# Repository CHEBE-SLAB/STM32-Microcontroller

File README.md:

# STM32-Microcontroller
STM32 Microcontroller project files using KiCAD, Gerber files included

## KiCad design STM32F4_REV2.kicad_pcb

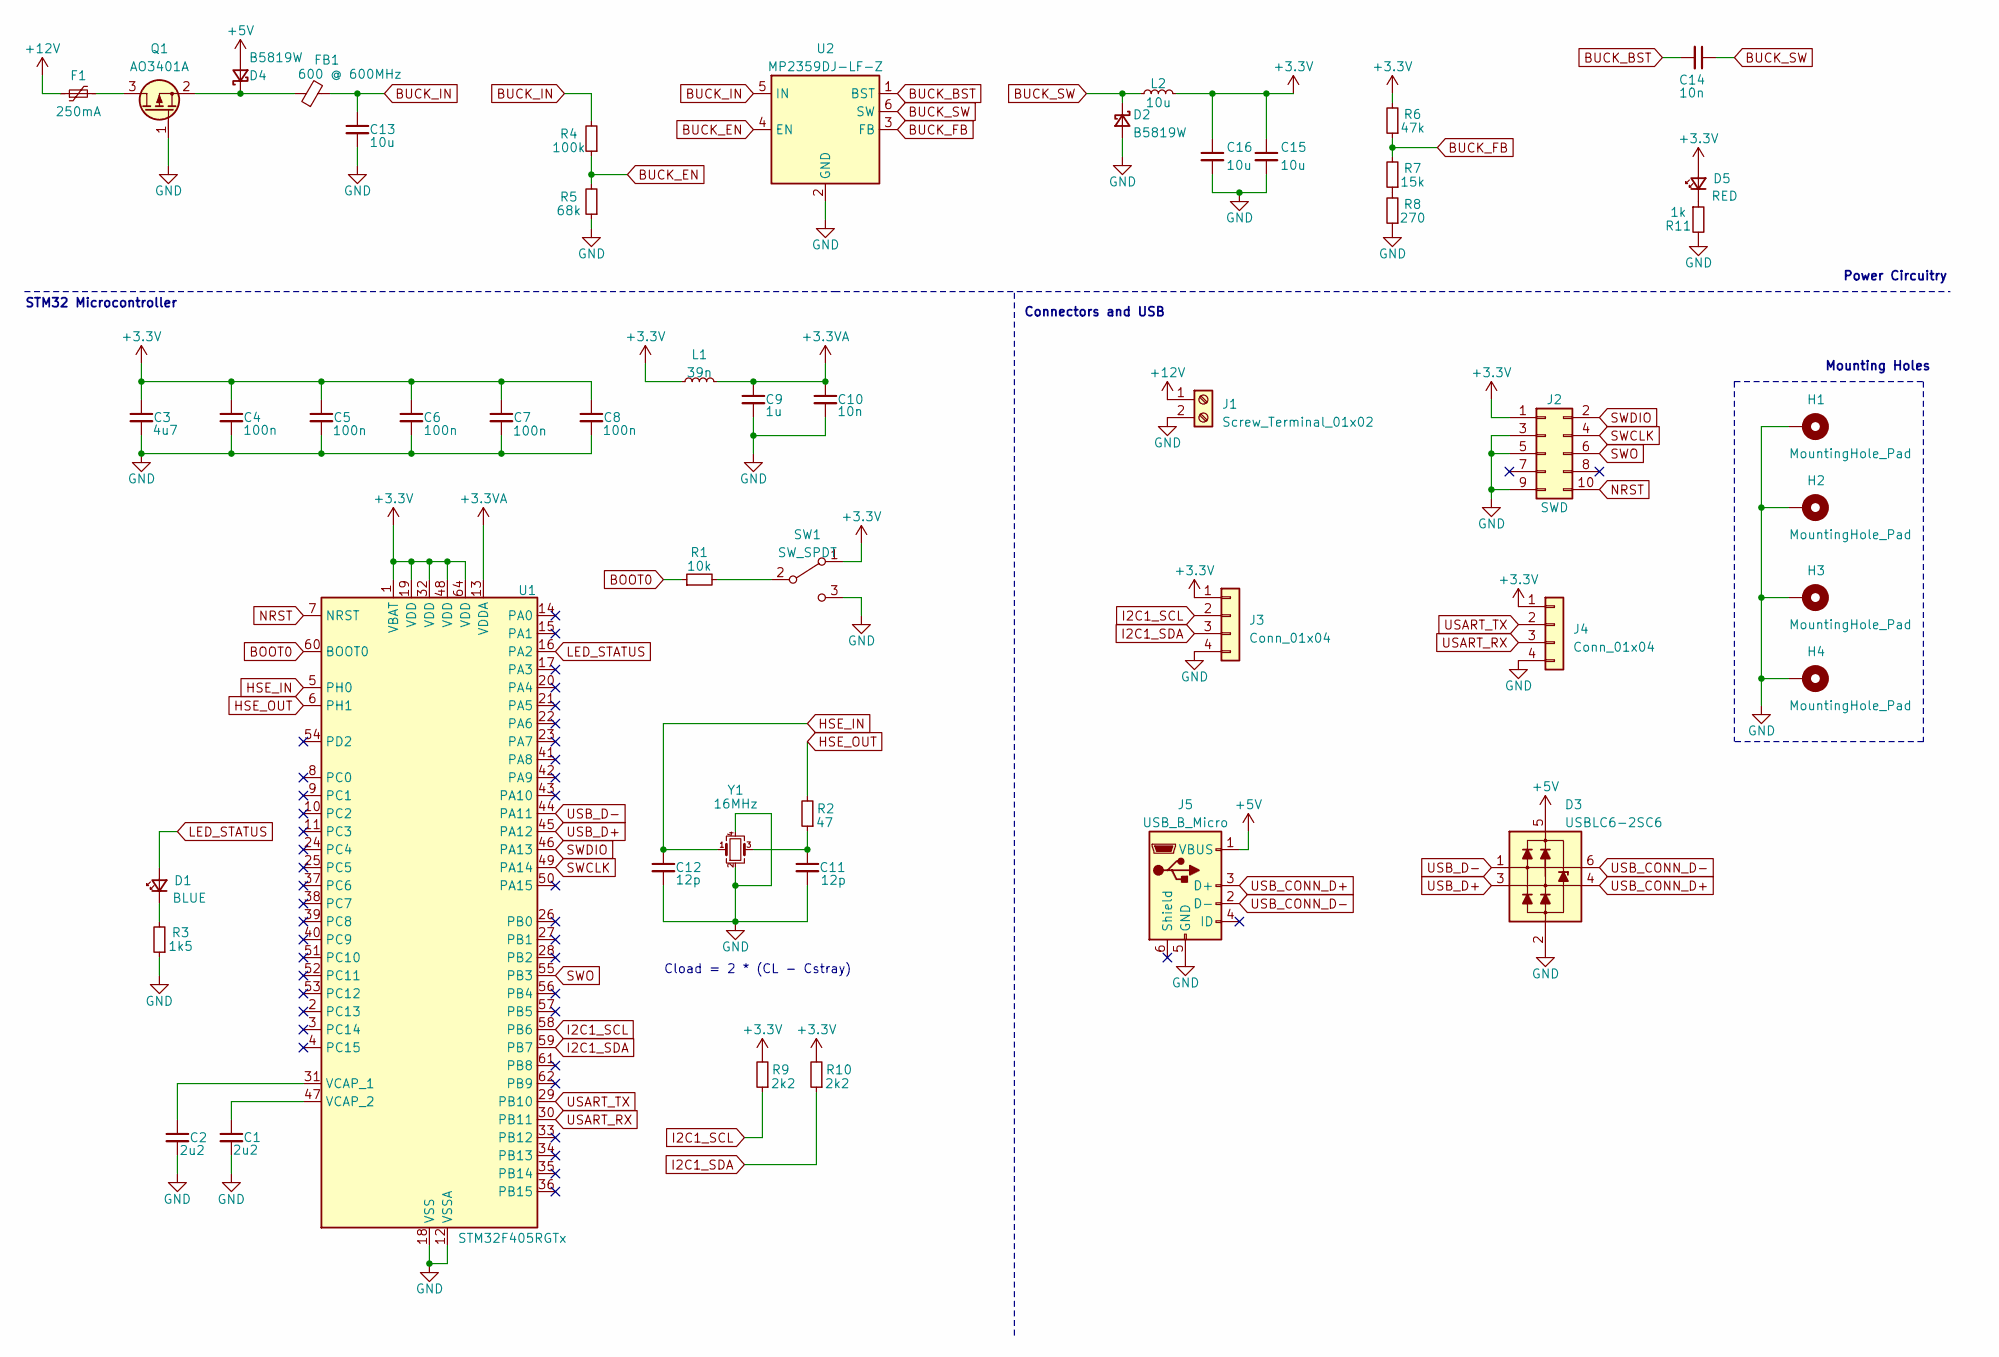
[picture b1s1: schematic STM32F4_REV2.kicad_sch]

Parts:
C1, C2: 2u2; C_0603_1608Metric
C3: 4u7; C_0201_0603Metric
C4, C5, C6, C7, C8: 100n; C_01005_0402Metric
C9: 1u; C_01005_0402Metric
C10: 10n; C_1206_3216Metric
C11, C12: 12p; C_0402_1005Metric
C13, C15, C16: 10u; C_1206_3216Metric
C14: 10n; C_0603_1608Metric
D1: BLUE; LED_0603_1608Metric
D2, D4: B5819W; D_SOD-123
D3: USBLC6-2SC6; SOT-23-6
D5: RED; LED_0603_1608Metric
F1: 250mA; Fuse_1206_3216Metric
FB1: 600 @ 600MHz; L_0805_2012Metric
H1, H2, H3, H4: MountingHole_Pad; MountingHole_4.5mm_Pad_Via
J1: Screw_Terminal_01x02; TerminalBlock_Phoenix_PT-1,5-2-3.5-H_1x02_P3.50mm_Horizontal
J2: SWD; PinSocket_2x05_P1.27mm_Vertical_SMD
J3, J4: Conn_01x04; Molex_PicoBlade_53048-0410_1x04_P1.25mm_Horizontal
J5: USB_B_Micro; USB_Micro-B_GCT_USB3076-30-A
L1: 39n; L_0402_1005Metric
L2: 10u; L_Sunlord_MWSA0518S
Q1: AO3401A; SOT-23
R1: 10k; R_0402_1005Metric
R2: 47; R_0402_1005Metric
R3: 1k5; R_0201_0603Metric
R4: 100k; R_0201_0603Metric
R5: 68k; R_0201_0603Metric
R6: 47k; R_0603_1608Metric
R7: 15k; R_0603_1608Metric
R8: 270; R_0603_1608Metric
R9, R10: 2k2; R_0402_1005Metric
R11: 1k; R_0603_1608Metric
SW1: SW_SPDT; SW_SPDT_PCM12
U1: STM32F405RGTx; LQFP-64_10x10mm_P0.5mm
U2: MP2359DJ-LF-Z; SOT-23-6
Y1: 16MHz; Crystal_SMD_3225-4Pin_3.2x2.5mm

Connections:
+3.3V: C3.1, C4.1, C5.1, C6.1, C7.1, C8.1, C15.1, C16.1, D5.2 (A), J2.1, J3.1, J4.1, L1.1, L2.2, R6.2, R9.2, R10.2, SW1.1 (A), U1.1 (VBAT), U1.19 (VDD), U1.32 (VDD), U1.48 (VDD), U1.64 (VDD)
+3.3VA: C9.1, C10.1, L1.2, U1.13 (VDDA)
+5V: D3.5 (VP), D4.2 (A), J5.1 (VBUS)
+12V: F1.1, J1.1
BOOT0: R1.1, U1.60 (BOOT0)
BUCK_BST: C14.2, U2.1 (BST)
BUCK_EN: R4.1, R5.2, U2.4 (EN)
BUCK_FB: R6.1, R7.2, U2.3 (FB)
BUCK_IN: C13.1, FB1.2, R4.2, U2.5 (IN)
BUCK_SW: C14.1, D2.1 (K), L2.1, U2.6 (SW)
GND: C1.2, C2.2, C3.2, C4.2, C5.2, C6.2, C7.2, C8.2, C9.2, C10.2, C11.2, C12.2, C13.2, C15.2, C16.2, D2.2 (A), D3.2 (VN), H1.1, H2.1, H3.1, H4.1, J1.2, J2.3, J2.5, J2.9, J3.4, J4.4, J5.5 (GND), Q1.1 (G), R3.1, R5.1, R8.1, R11.2, SW1.3 (C), U1.12 (VSSA), U1.18 (VSS), U1.63 (VSS), U2.2 (GND), Y1.2, Y1.4
HSE_IN: C12.1, U1.5 (PH0), Y1.1
HSE_OUT: R2.2, U1.6 (PH1)
I2C1_SCL: J3.2, R9.1, U1.58 (PB6)
I2C1_SDA: J3.3, R10.1, U1.59 (PB7)
LED_STATUS: D1.2 (A), U1.16 (PA2)
NRST: J2.10, U1.7 (NRST)
unnamed: C11.1, R2.1, Y1.3
unnamed: D1.1 (K), R3.2
unnamed: D4.1 (K), FB1.1, Q1.2 (S)
unnamed: D5.1 (K), R11.1
unnamed: F1.2, Q1.3 (D)
unnamed: R7.1, R8.2
unnamed: R1.2, SW1.2 (B)
unnamed: C2.1, U1.31 (VCAP_1)
unnamed: C1.1, U1.47 (VCAP_2)
SWCLK: J2.4, U1.49 (PA14)
SWDIO: J2.2, U1.46 (PA13)
SWO: J2.6, U1.55 (PB3)
USART_RX: J4.3, U1.30 (PB11)
USART_TX: J4.2, U1.29 (PB10)
USB_CONN_D+: D3.4 (L2), J5.3 (D+)
USB_CONN_D-: D3.6 (L1), J5.2 (D-)
USB_D+: D3.3 (L2), U1.45 (PA12)
USB_D-: D3.1 (L1), U1.44 (PA11)

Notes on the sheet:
Mounting Holes
STM32 Microcontroller
Connectors and USB
Power Circuitry
Cload = 2 * (CL - Cstray)

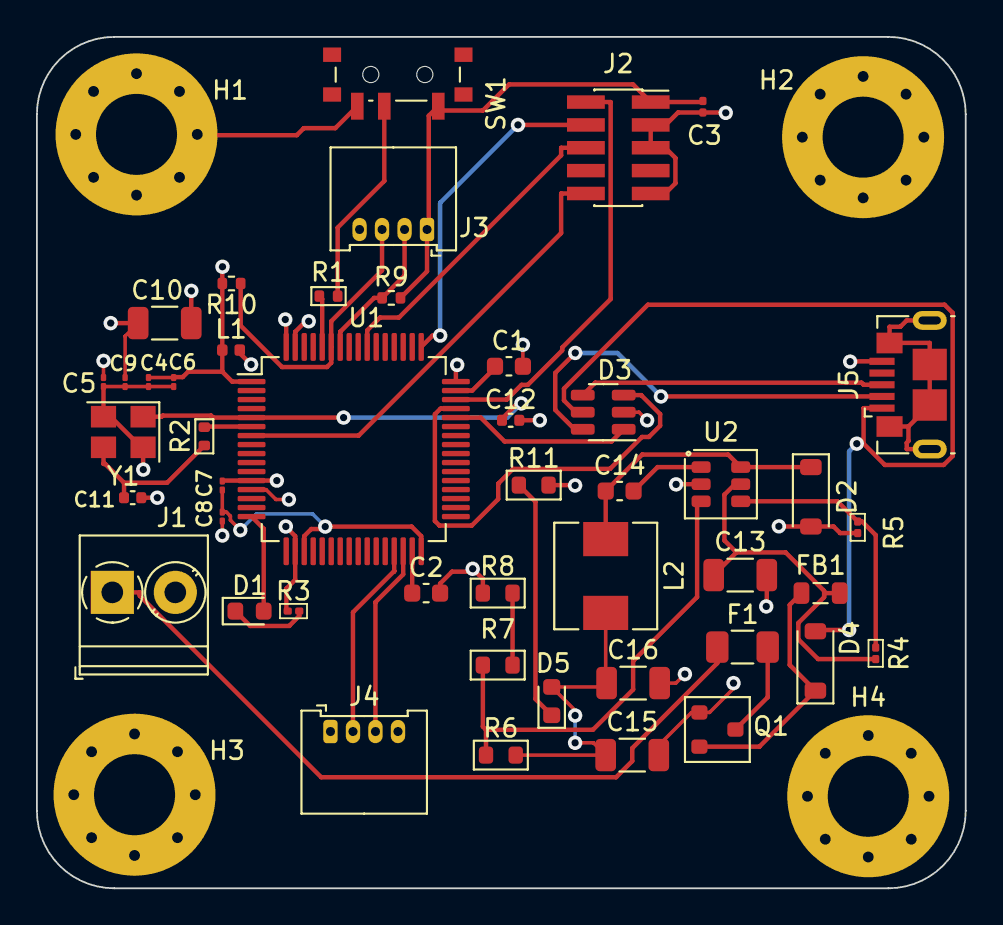
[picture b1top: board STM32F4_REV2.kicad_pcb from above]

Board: 4 copper layers, 51.6 x 47.3 mm, 50 parts (0 on the bottom side), 35 nets.
